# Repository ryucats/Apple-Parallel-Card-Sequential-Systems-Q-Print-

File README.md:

# Apple-Parallel-Card-Sequential-Systems-Q-Print-

An Apple ][ parallel interface card based on Sequential Systems' Q-Print card.

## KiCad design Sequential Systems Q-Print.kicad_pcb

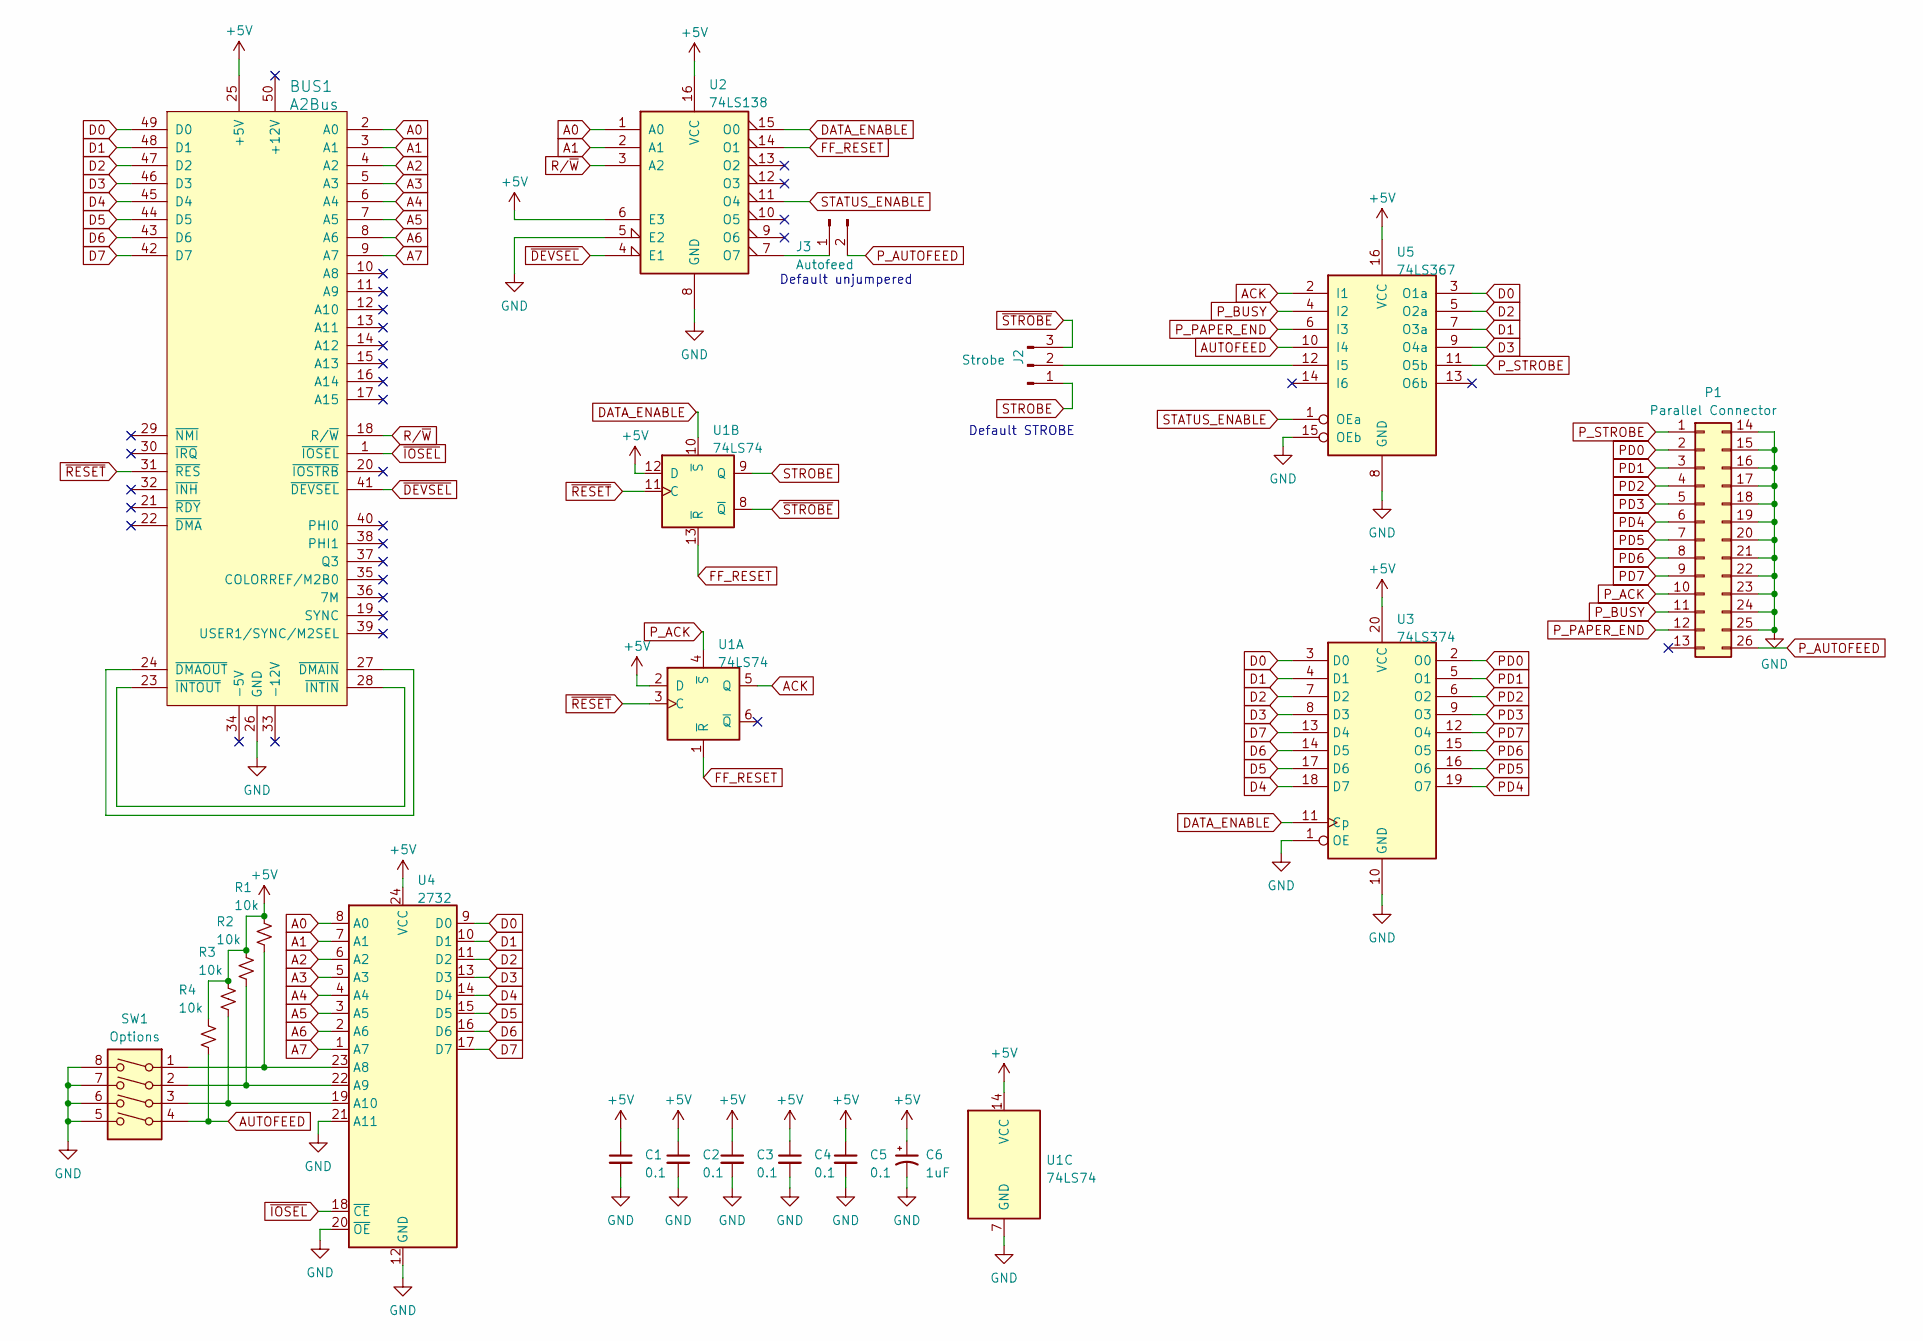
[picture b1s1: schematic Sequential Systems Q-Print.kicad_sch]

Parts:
BUS1: A2Bus; Male_Card-Edge_50_pin__100_mil
C1, C2, C3, C4, C5: 0.1; C_Axial_L3.8mm_D2.6mm_P7.50mm_Horizontal
C6: 1uF; CP_Radial_D7.5mm_P2.50mm
J2: Strobe; PinHeader_1x03_P2.54mm_Vertical
J3: Autofeed; PinHeader_1x02_P2.54mm_Vertical
P1: Parallel Connector
R1, R2, R3, R4: 10k; R_Axial_DIN0207_L6.3mm_D2.5mm_P10.16mm_Horizontal
SW1: Options; SW_DIP_SPSTx04_Slide_6.7x11.72mm_W7.62mm_P2.54mm_LowProfile
U1: 74LS74; DIP-14_W7.62mm
U2: 74LS138; DIP-16_W7.62mm
U3: 74LS374; DIP-20_W7.62mm
U4: 2732; DIP-24_W15.24mm
U5: 74LS367; DIP-16_W7.62mm

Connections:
+5V: BUS1.25 (+5V), C1.1, C2.1, C3.1, C4.1, C5.1, C6.1, R1.1, R2.1, R3.1, R4.1, U1.2 (D), U1.12 (D), U1.14 (VCC), U2.6 (E3), U2.16 (VCC), U3.20 (VCC), U4.24 (VCC), U5.16 (VCC)
A0: BUS1.2 (A0), U2.1 (A0), U4.8 (A0)
A1: BUS1.3 (A1), U2.2 (A1), U4.7 (A1)
A2: BUS1.4 (A2), U4.6 (A2)
A3: BUS1.5 (A3), U4.5 (A3)
A4: BUS1.6 (A4), U4.4 (A4)
A5: BUS1.7 (A5), U4.3 (A5)
A6: BUS1.8 (A6), U4.2 (A6)
A7: BUS1.9 (A7), U4.1 (A7)
ACK: U1.5 (Q), U5.2 (I1)
AUTOFEED: R4.2, SW1.4, U5.10 (I4)
D0: BUS1.49 (D0), U3.3 (D0), U4.9 (D0), U5.3 (O1a)
D1: BUS1.48 (D1), U3.4 (D1), U4.10 (D1), U5.7 (O3a)
D2: BUS1.47 (D2), U3.7 (D2), U4.11 (D2), U5.5 (O2a)
D3: BUS1.46 (D3), U3.8 (D3), U4.13 (D3), U5.9 (O4a)
D4: BUS1.45 (D4), U3.18 (D7), U4.14 (D4)
D5: BUS1.44 (D5), U3.17 (D6), U4.15 (D5)
D6: BUS1.43 (D6), U3.14 (D5), U4.16 (D6)
D7: BUS1.42 (D7), U3.13 (D4), U4.17 (D7)
DATA_ENABLE: U1.10 (~S), U2.15 (O0), U3.11 (Cp)
FF_RESET: U1.1 (~R), U1.13 (~R), U2.14 (O1)
GND: BUS1.26 (GND), C1.2, C2.2, C3.2, C4.2, C5.2, C6.2, P1.14, P1.15, P1.16, P1.17, P1.18, P1.19, P1.20, P1.21, P1.22, P1.23, P1.24, P1.25, SW1.5, SW1.6, SW1.7, SW1.8, U1.7 (GND), U2.5 (E2), U2.8 (GND), U3.1 (OE), U3.10 (GND), U4.12 (GND), U4.20 (~OE), U4.21 (A11), U5.8 (GND), U5.15 (OEb)
unnamed: BUS1.24 (~DMAOUT), BUS1.27 (~DMAIN)
unnamed: BUS1.23 (~INTOUT), BUS1.28 (~INTIN)
unnamed: J2.2, U5.12 (I5)
unnamed: J3.1, U2.7 (O7)
unnamed: R1.2, SW1.1, U4.23 (A8)
unnamed: R2.2, SW1.2, U4.22 (A9)
unnamed: R3.2, SW1.3, U4.19 (A10)
PD0: P1.2, U3.2 (O0)
PD1: P1.3, U3.5 (O1)
PD2: P1.4, U3.6 (O2)
PD3: P1.5, U3.9 (O3)
PD4: P1.6, U3.19 (O7)
PD5: P1.7, U3.16 (O6)
PD6: P1.8, U3.15 (O5)
PD7: P1.9, U3.12 (O4)
P_ACK: P1.10, U1.4 (~S)
P_AUTOFEED: J3.2, P1.26
P_BUSY: P1.11, U5.4 (I2)
P_PAPER_END: P1.12, U5.6 (I3)
P_STROBE: P1.1, U5.11 (O5b)
R/~W: BUS1.18 (R/~W), U2.3 (A2)
STATUS_ENABLE: U2.11 (O4), U5.1 (OEa)
STROBE: J2.1, U1.9 (Q)
~DEVSEL: BUS1.41 (~DEVSEL), U2.4 (E1)
~IOSEL: BUS1.1 (~IOSEL), U4.18 (~CE)
~RESET: BUS1.31 (~RES), U1.3 (C), U1.11 (C)
~STROBE: J2.3, U1.8 (~Q)

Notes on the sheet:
Default STROBE
Default unjumpered

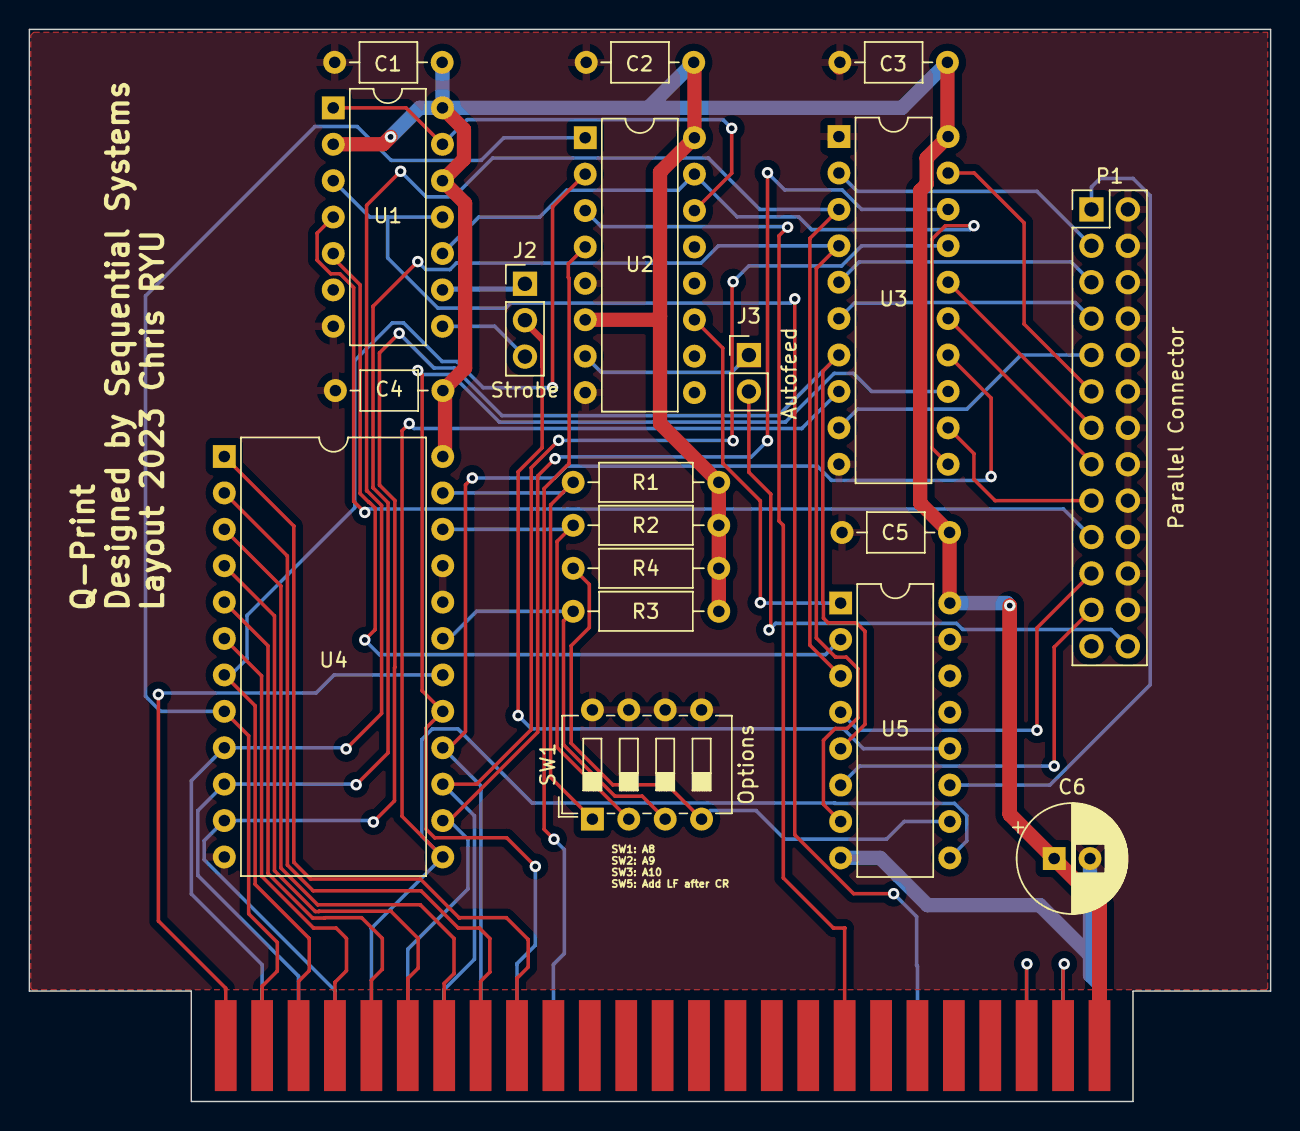
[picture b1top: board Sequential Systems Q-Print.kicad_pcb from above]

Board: 2 copper layers, 86.6 x 74.8 mm, 20 parts (0 on the bottom side), 49 nets.

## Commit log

2023-04-08 Initial commit.
2023-04-08 Remove WIP files.
2023-04-08 Add image.
